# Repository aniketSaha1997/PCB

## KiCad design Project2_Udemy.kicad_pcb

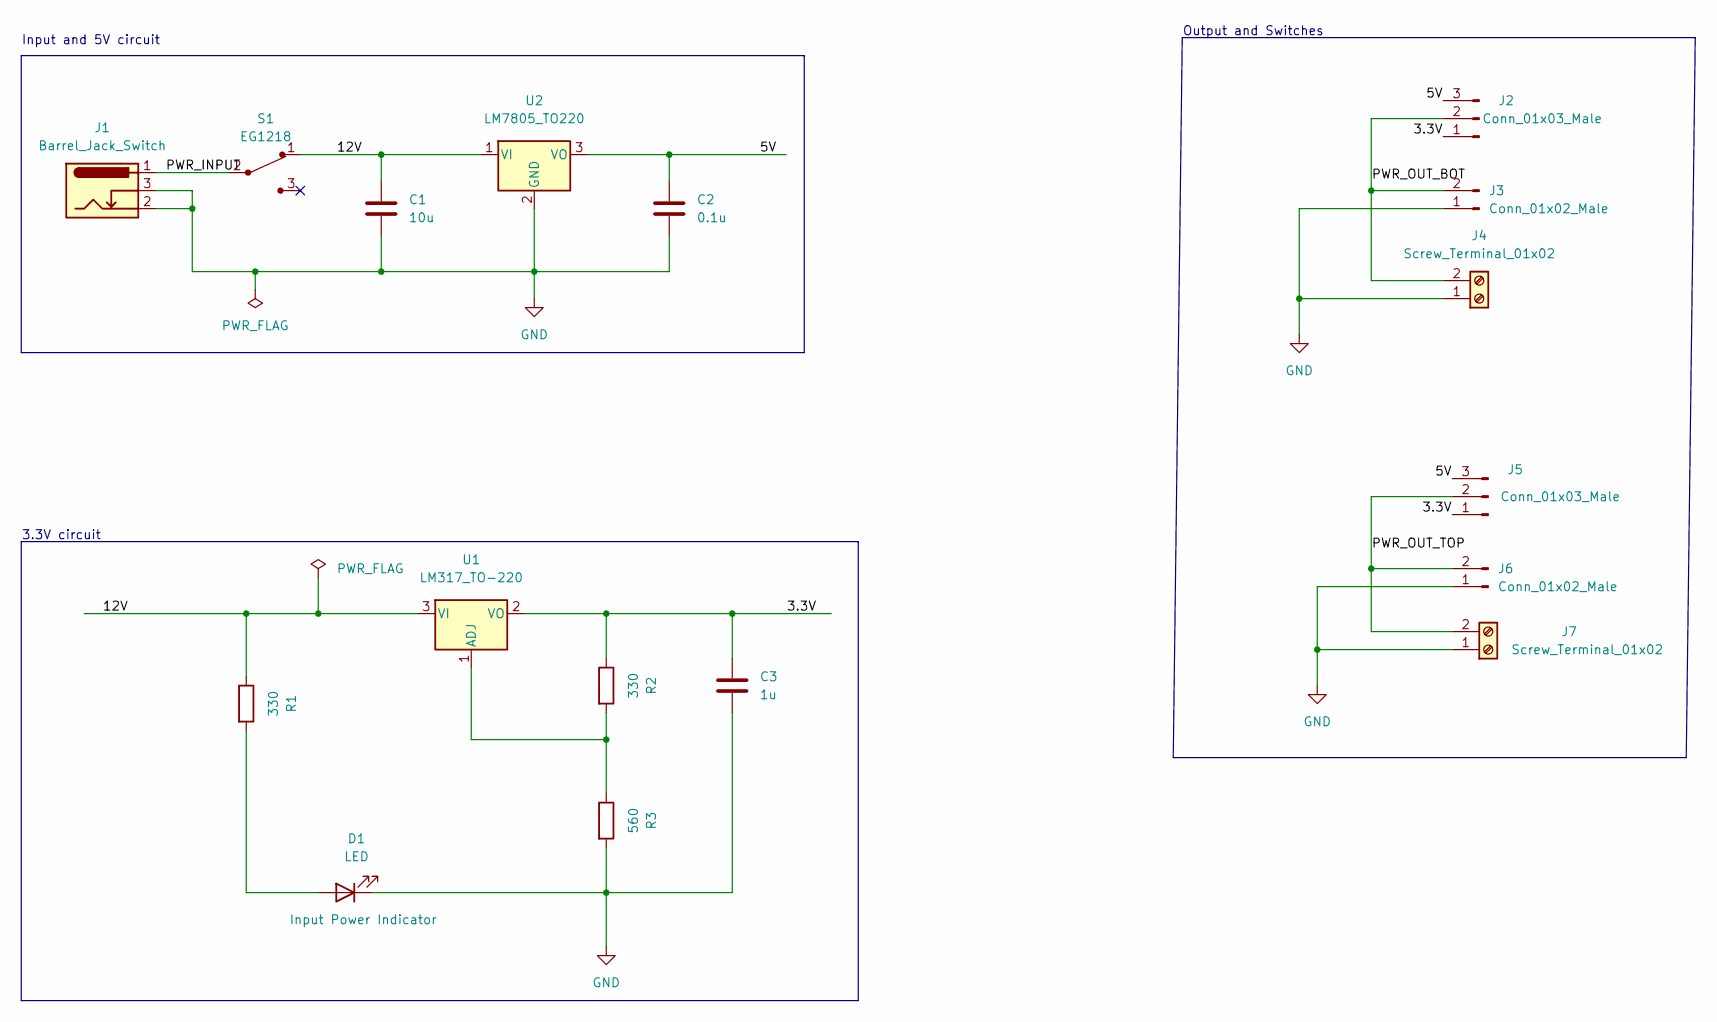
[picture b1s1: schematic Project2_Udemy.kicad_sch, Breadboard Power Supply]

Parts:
C1: 10u; C_Disc_D3.0mm_W1.6mm_P2.50mm
C2: 0.1u; C_Disc_D3.0mm_W1.6mm_P2.50mm
C3: 1u; C_Disc_D3.0mm_W1.6mm_P2.50mm
D1: LED; LED_D5.0mm
J1: Barrel_Jack_Switch; BarrelJack_Horizontal
J2, J5: Conn_01x03_Male; PinHeader_1x03_P2.54mm_Vertical
J3, J6: Conn_01x02_Male; PinHeader_1x02_P2.54mm_Vertical
J4, J7: Screw_Terminal_01x02; TerminalBlock_bornier-2_P5.08mm
R1, R2: 330; R_Axial_DIN0207_L6.3mm_D2.5mm_P7.62mm_Horizontal
R3: 560; R_Axial_DIN0207_L6.3mm_D2.5mm_P7.62mm_Horizontal
S1: EG1218; Switch_Slide_11.6x4mm_EG1218; MPN EG1218; Digi-Key_PN EG1903-ND
U1: LM317_TO-220; TO-220-3_Vertical
U2: LM7805_TO220; TO-220-3_Vertical

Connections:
/3.3V: C3.1, J2.1, J5.1, R2.1, U1.2 (VO)
/5V: C2.1, J2.3, J5.3, U2.3 (VO)
/12V: C1.1, R1.1, S1.1, U1.3 (VI), U2.1 (VI)
/PWR_INPUT: J1.1, S1.2
/PWR_OUT_BOT: J2.2, J3.2, J4.2
/PWR_OUT_TOP: J5.2, J6.2, J7.2
GND: C1.2, C2.2, C3.2, D1.1 (K), J1.2, J1.3, J3.1, J4.1, J6.1, J7.1, R3.2, U2.2 (GND)
unnamed: D1.2 (A), R1.2
unnamed: R2.2, R3.1, U1.1 (ADJ)

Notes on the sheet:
Output and Switches
3.3V circuit
Input and 5V circuit

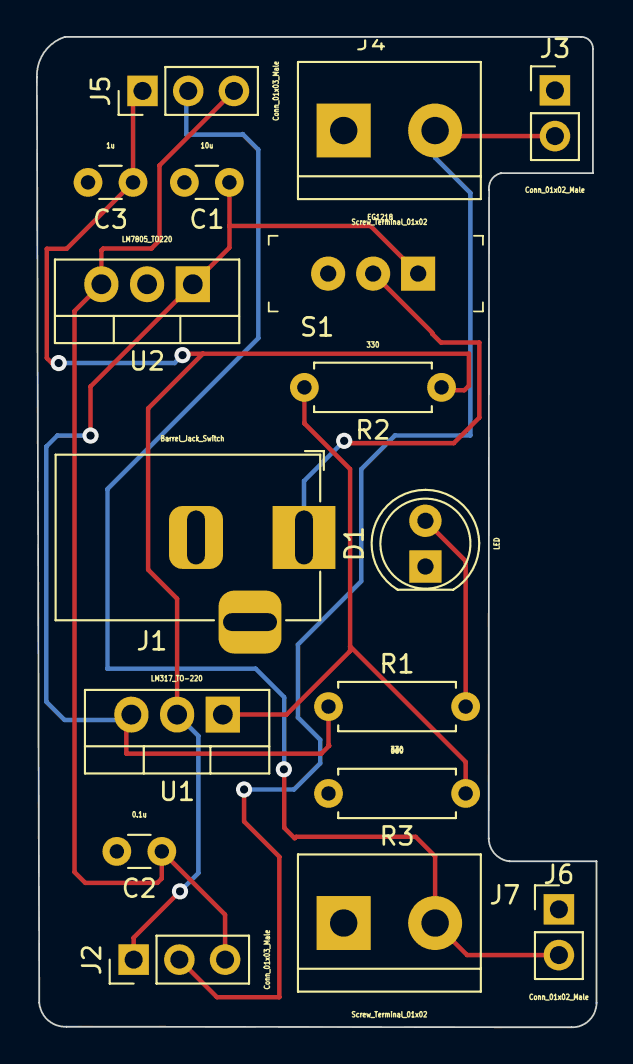
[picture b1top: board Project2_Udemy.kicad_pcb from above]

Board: 2 copper layers, 31.1 x 55.0 mm, 17 parts (0 on the bottom side), 9 nets.
